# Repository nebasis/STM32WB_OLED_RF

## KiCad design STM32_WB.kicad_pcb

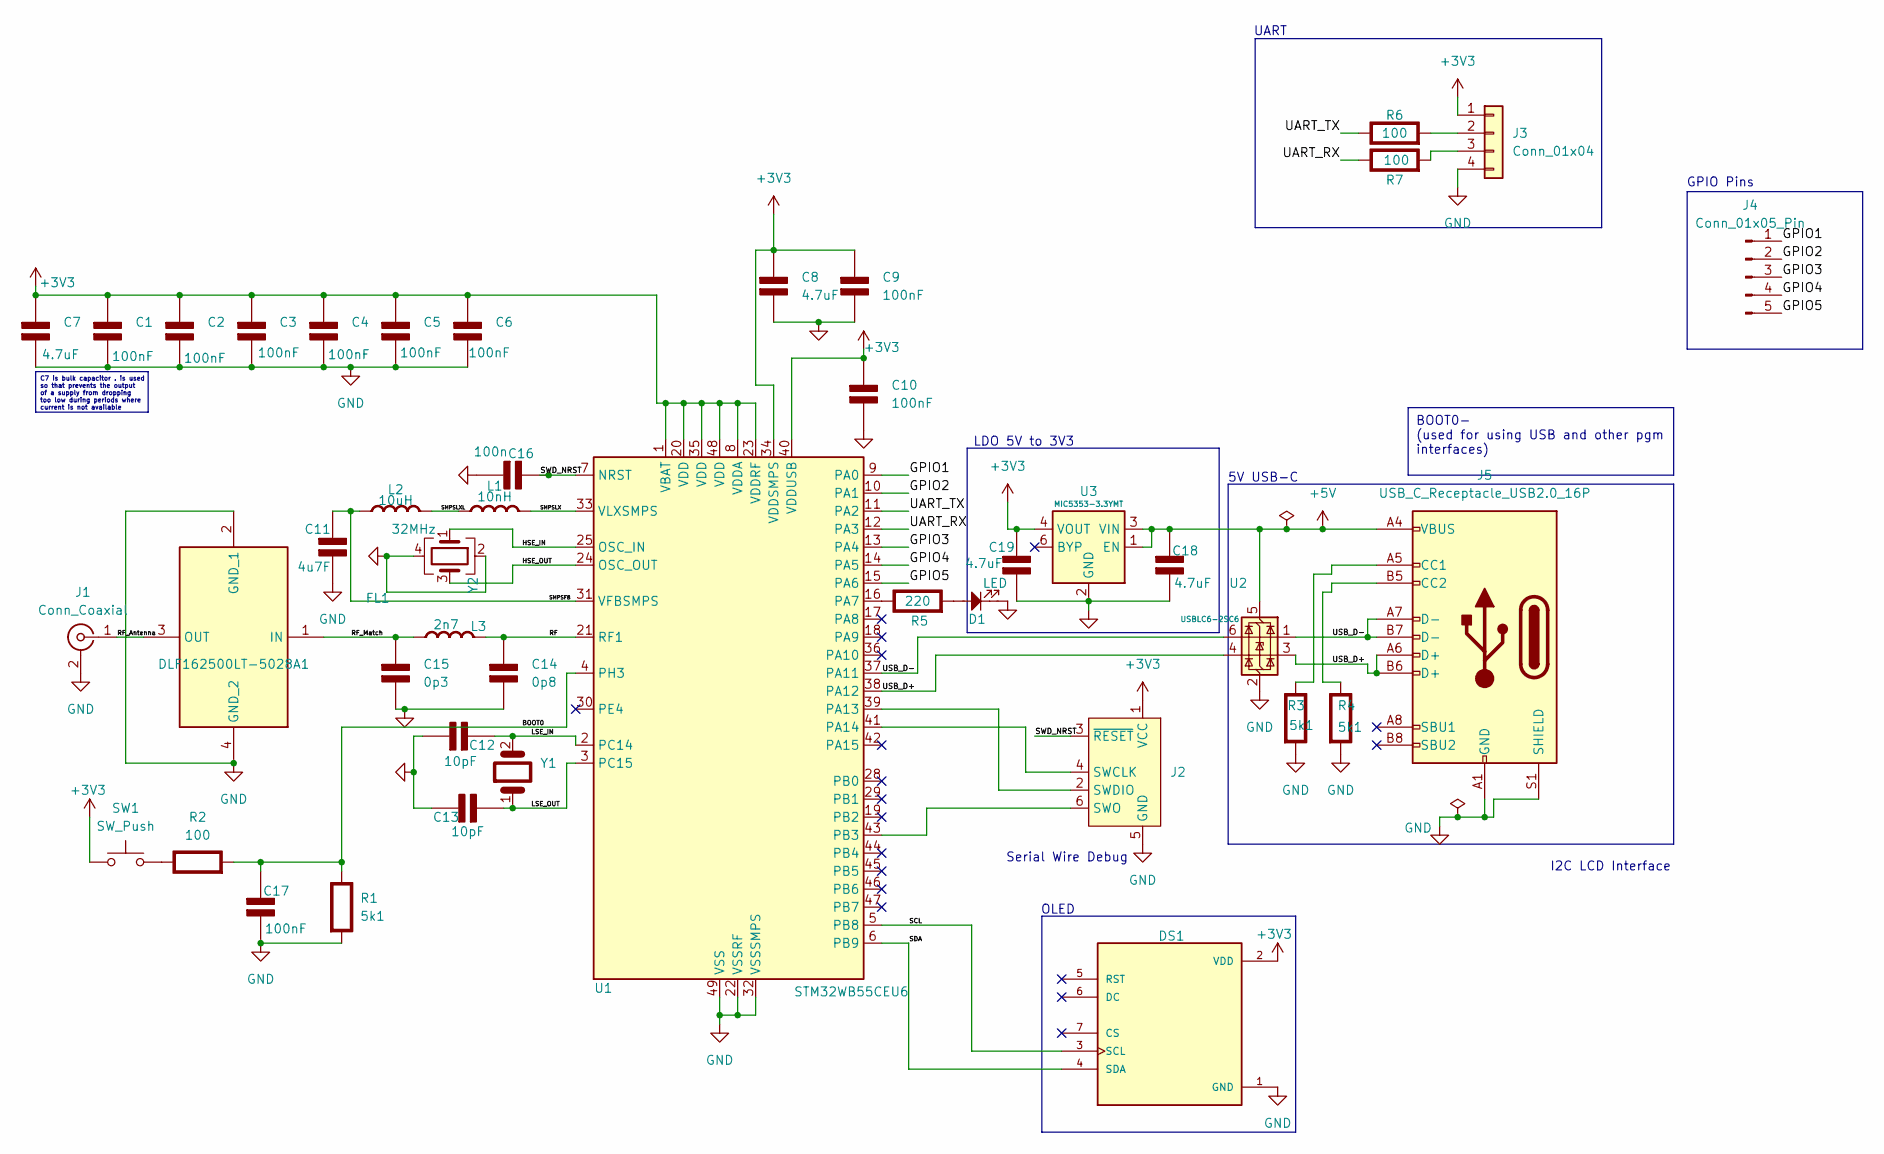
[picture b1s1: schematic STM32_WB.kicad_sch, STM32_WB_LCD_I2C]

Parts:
C1, C2, C3, C4, C5, C6, C9, C10, C17: 100nF; C_0402_1005Metric; Rating V
C7, C8, C18, C19: 4.7uF; C_0603_1608Metric; Rating V
C11: 4u7F; C_0603_1608Metric; Rating V
C12, C13: 10pF; C_0402_1005Metric; Rating V
C14: 0p8; C_0402_1005Metric; Rating V
C15: 0p3; C_0402_1005Metric; Rating V
C16: 100n; C_0402_1005Metric; Rating V
D1: LED; LED_0402_1005Metric_Pad0.77x0.64mm_HandSolder
DS1: AOM12864A0-1.54WW-ANO; LCD_AOM12864A0-1.54WW-ANO; PARTREV O
FL1: DLF162500LT-5028A1; DLF162500LT5028A1; Mouser Part Number 810-DLF16250LT5028A1
J1: Conn_Coaxial; MMCX_Molex_73415-1471_Vertical
J2: Conn_ARM_SWD_TagConnect_TC2030; Tag-Connect_TC2030-IDC-FP_2x03_P1.27mm_Vertical
J3: Conn_01x04; PinHeader_1x04_P1.00mm_Vertical; Part Number 1-0401FBV0T
J4: Conn_01x05_Pin; PinHeader_1x05_P2.54mm_Vertical
J5: USB_C_Receptacle_USB2.0_16P; USB_C_Receptacle_GCT_USB4105-xx-A_16P_TopMnt_Horizontal
L1: 10nH; L_0402_1005Metric; Rating A
L2: 10uH; L_0805_2012Metric; Rating A
L3: 2n7; L_0402_1005Metric; Rating A
R1, R3, R4: 5k1; R_0402_1005Metric; Rating W
R2, R6, R7: 100; R_0402_1005Metric; Rating W
R5: 220; R_0402_1005Metric; Rating W
SW1: SW_Push; SW_Push_SPST_NO_Alps_SKRK
U1: STM32WB55CEU6; QFN-48-1EP_7x7mm_P0.5mm_EP5.6x5.6mm
U2: USBLC6-2SC6; SOT-23-6
U3: MIC5353-3.3YMT; MLF-6-1EP_1.6x1.6mm_P0.5mm_EP0.5x1.26mm
Y1: 32.768kHz; Crystal_SMD_2016-4Pin_2.0x1.6mm
Y2: 32MHz; Crystal_SMD_2016-4Pin_2.0x1.6mm

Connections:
+3V3: C1.1 (+), C2.1 (+), C3.1 (+), C4.1 (+), C5.1 (+), C6.1 (+), C7.1 (+), C8.1 (+), C9.1 (+), C10.1 (+), C19.1 (+), DS1.2 (VDD), J2.1 (VCC), J3.1, SW1.1, U1.1 (VBAT), U1.8 (VDDA), U1.20 (VDD), U1.23 (VDDRF), U1.34 (VDDSMPS), U1.35 (VDD), U1.40 (VDDUSB), U1.48 (VDD), U3.4 (VOUT)
+5V: C18.1 (+), J5.A4 (VBUS), J5.A9 (VBUS), J5.B4 (VBUS), J5.B9 (VBUS), U2.5 (VBUS), U3.1 (EN), U3.3 (VIN)
/BOOT0: C17.1 (+), R1.1 (+), R2.2 (-), U1.4 (PH3)
/GPIO1: J4.1, U1.9 (PA0)
/GPIO2: J4.2, U1.10 (PA1)
/GPIO3: J4.3, U1.13 (PA4)
/GPIO4: J4.4, U1.14 (PA5)
/GPIO5: J4.5, U1.15 (PA6)
/HSE_IN: U1.25 (OSC_IN), Y2.1
/HSE_OUT: U1.24 (OSC_OUT), Y2.3
/LSE_IN: C12.2 (-), U1.2 (PC14), Y1.2
/LSE_OUT: C13.2 (-), U1.3 (PC15), Y1.1
/RF: C14.1 (+), L3.2 (-), U1.21 (RF1)
/RF_Antenna: FL1.3 (OUT), J1.1 (In)
/RF_Match: C15.1 (+), FL1.1 (IN), L3.1 (+)
/SCL: DS1.3 (SCL), U1.5 (PB8)
/SDA: DS1.4 (SDA), U1.6 (PB9)
/SMPSFB: C11.1 (+), L2.1 (+), U1.31 (VFBSMPS)
/SMPSLX: L1.2 (-), U1.33 (VLXSMPS)
/SMPSLXL: L1.1 (+), L2.2 (-)
/SWD_NRST: C16.1 (+), J2.3 (~RESET), U1.7 (NRST)
/UART_RX: R7.1 (+), U1.12 (PA3)
/UART_TX: R6.1 (+), U1.11 (PA2)
/USB_D+: J5.A6 (D+), J5.B6 (D+), U1.38 (PA12), U2.3 (I/O2), U2.4 (I/O2)
/USB_D-: J5.A7 (D-), J5.B7 (D-), U1.37 (PA11), U2.1 (I/O1), U2.6 (I/O1)
GND: C1.2 (-), C2.2 (-), C3.2 (-), C4.2 (-), C5.2 (-), C6.2 (-), C7.2 (-), C8.2 (-), C9.2 (-), C10.2 (-), C11.2 (-), C12.1 (+), C13.1 (+), C14.2 (-), C15.2 (-), C16.2 (-), C17.2 (-), C18.2 (-), C19.2 (-), D1.1, DS1.1 (GND), FL1.2 (GND_1), FL1.4 (GND_2), J1.2 (Ext), J2.5 (GND), J3.4, J5.A1 (GND), J5.A12 (GND), J5.B1 (GND), J5.B12 (GND), J5.S1 (SHIELD), R1.2 (-), R3.2 (-), R4.2 (-), U1.22 (VSSRF), U1.32 (VSSSMPS), U1.49 (VSS), U2.2 (GND), U3.2 (GND), U3.7 (GND), Y2.2, Y2.4
unnamed: J2.4 (SWCLK), U1.41 (PA14)
unnamed: J2.2 (SWDIO), U1.39 (PA13)
unnamed: J2.6 (SWO), U1.43 (PB3)
unnamed: J3.2, R6.2 (-)
unnamed: J3.3, R7.2 (-)
unnamed: J5.A5 (CC1), R3.1 (+)
unnamed: J5.B5 (CC2), R4.1 (+)
unnamed: R2.1 (+), SW1.2
unnamed: R5.1 (+), U1.16 (PA7)
unnamed: D1.2, R5.2 (-)

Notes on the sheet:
C7 is bulk capacitor . is used so that prevents the output of a supply from dropping too low during periods where current is not available
BOOT0- (used for using USB and other pgm interfaces)
LDO 5V to 3V3
5V USB-C
OLED
I2C LCD Interface
GPIO Pins
Serial Wire Debug
UART

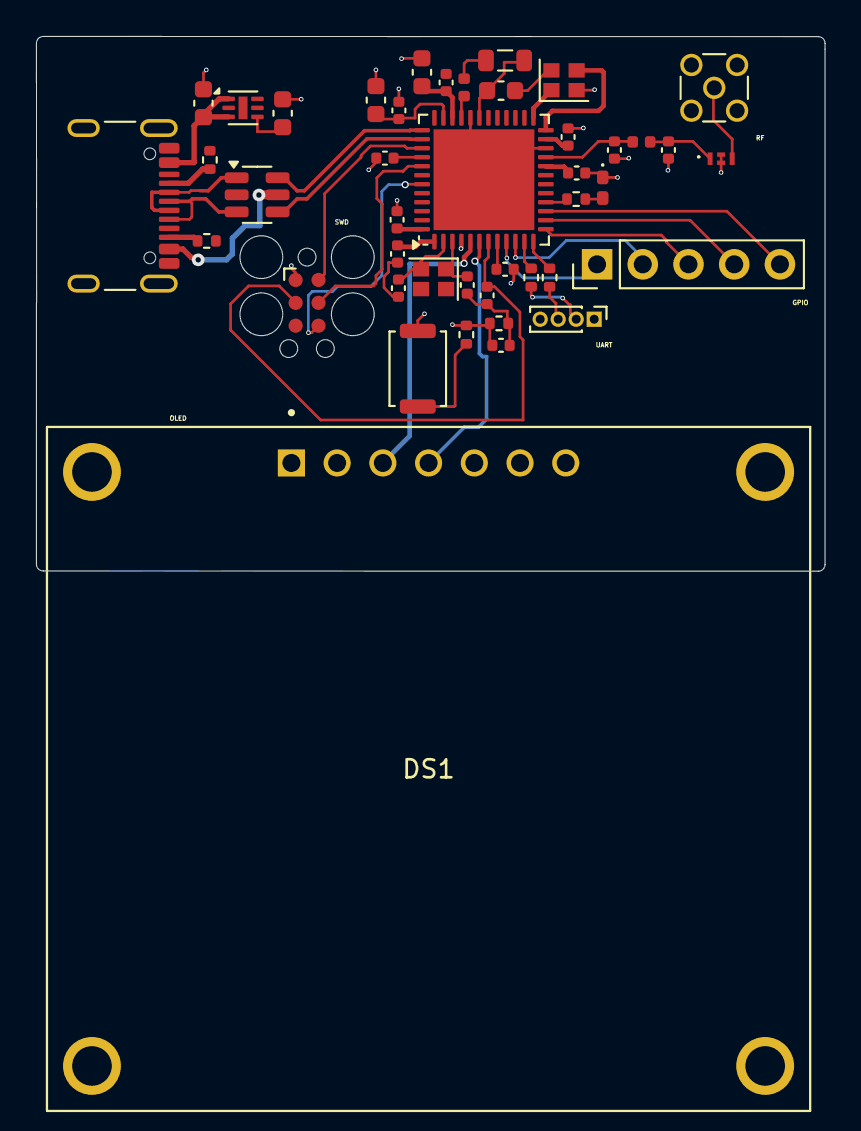
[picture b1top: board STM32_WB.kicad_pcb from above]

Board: 4 copper layers, 43.8 x 29.7 mm, 43 parts (0 on the bottom side), 36 nets.
